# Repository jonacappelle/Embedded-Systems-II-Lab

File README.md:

# LAB: Embedded Systems II

## SOFTWARE

- [IMU](https://github.com/jonacappelle/Embedded-Systems-II-Lab/tree/master/Jona%20-%20IMU%20and%20Main%20PCB/Embedded_II_ICM_20948)
- [Game](https://github.com/jonacappelle/Embedded-Systems-II-Lab/tree/master/Niels%20-%20Code%20spel/SLSTK3400A_blink)
- [LoRa](https://github.com/jonacappelle/Embedded-Systems-II-Lab/tree/master/Pieter%20-%20Connectivity%20and%20Visualisation)

## HARDWARE

[Main board](https://github.com/jonacappelle/Embedded-Systems-II-Lab/tree/master/Jona%20-%20IMU%20and%20Main%20PCB/EFM32_ICM20948_PCB)  
[Energy harvesting](https://github.com/jonacappelle/Embedded-Systems-II-Lab/tree/master/Daan%20-%20VoedingDesign%20PCB/schema_pcb)

### MAIN BOARD: µC + Compass + LoRa

### POWER BOARD

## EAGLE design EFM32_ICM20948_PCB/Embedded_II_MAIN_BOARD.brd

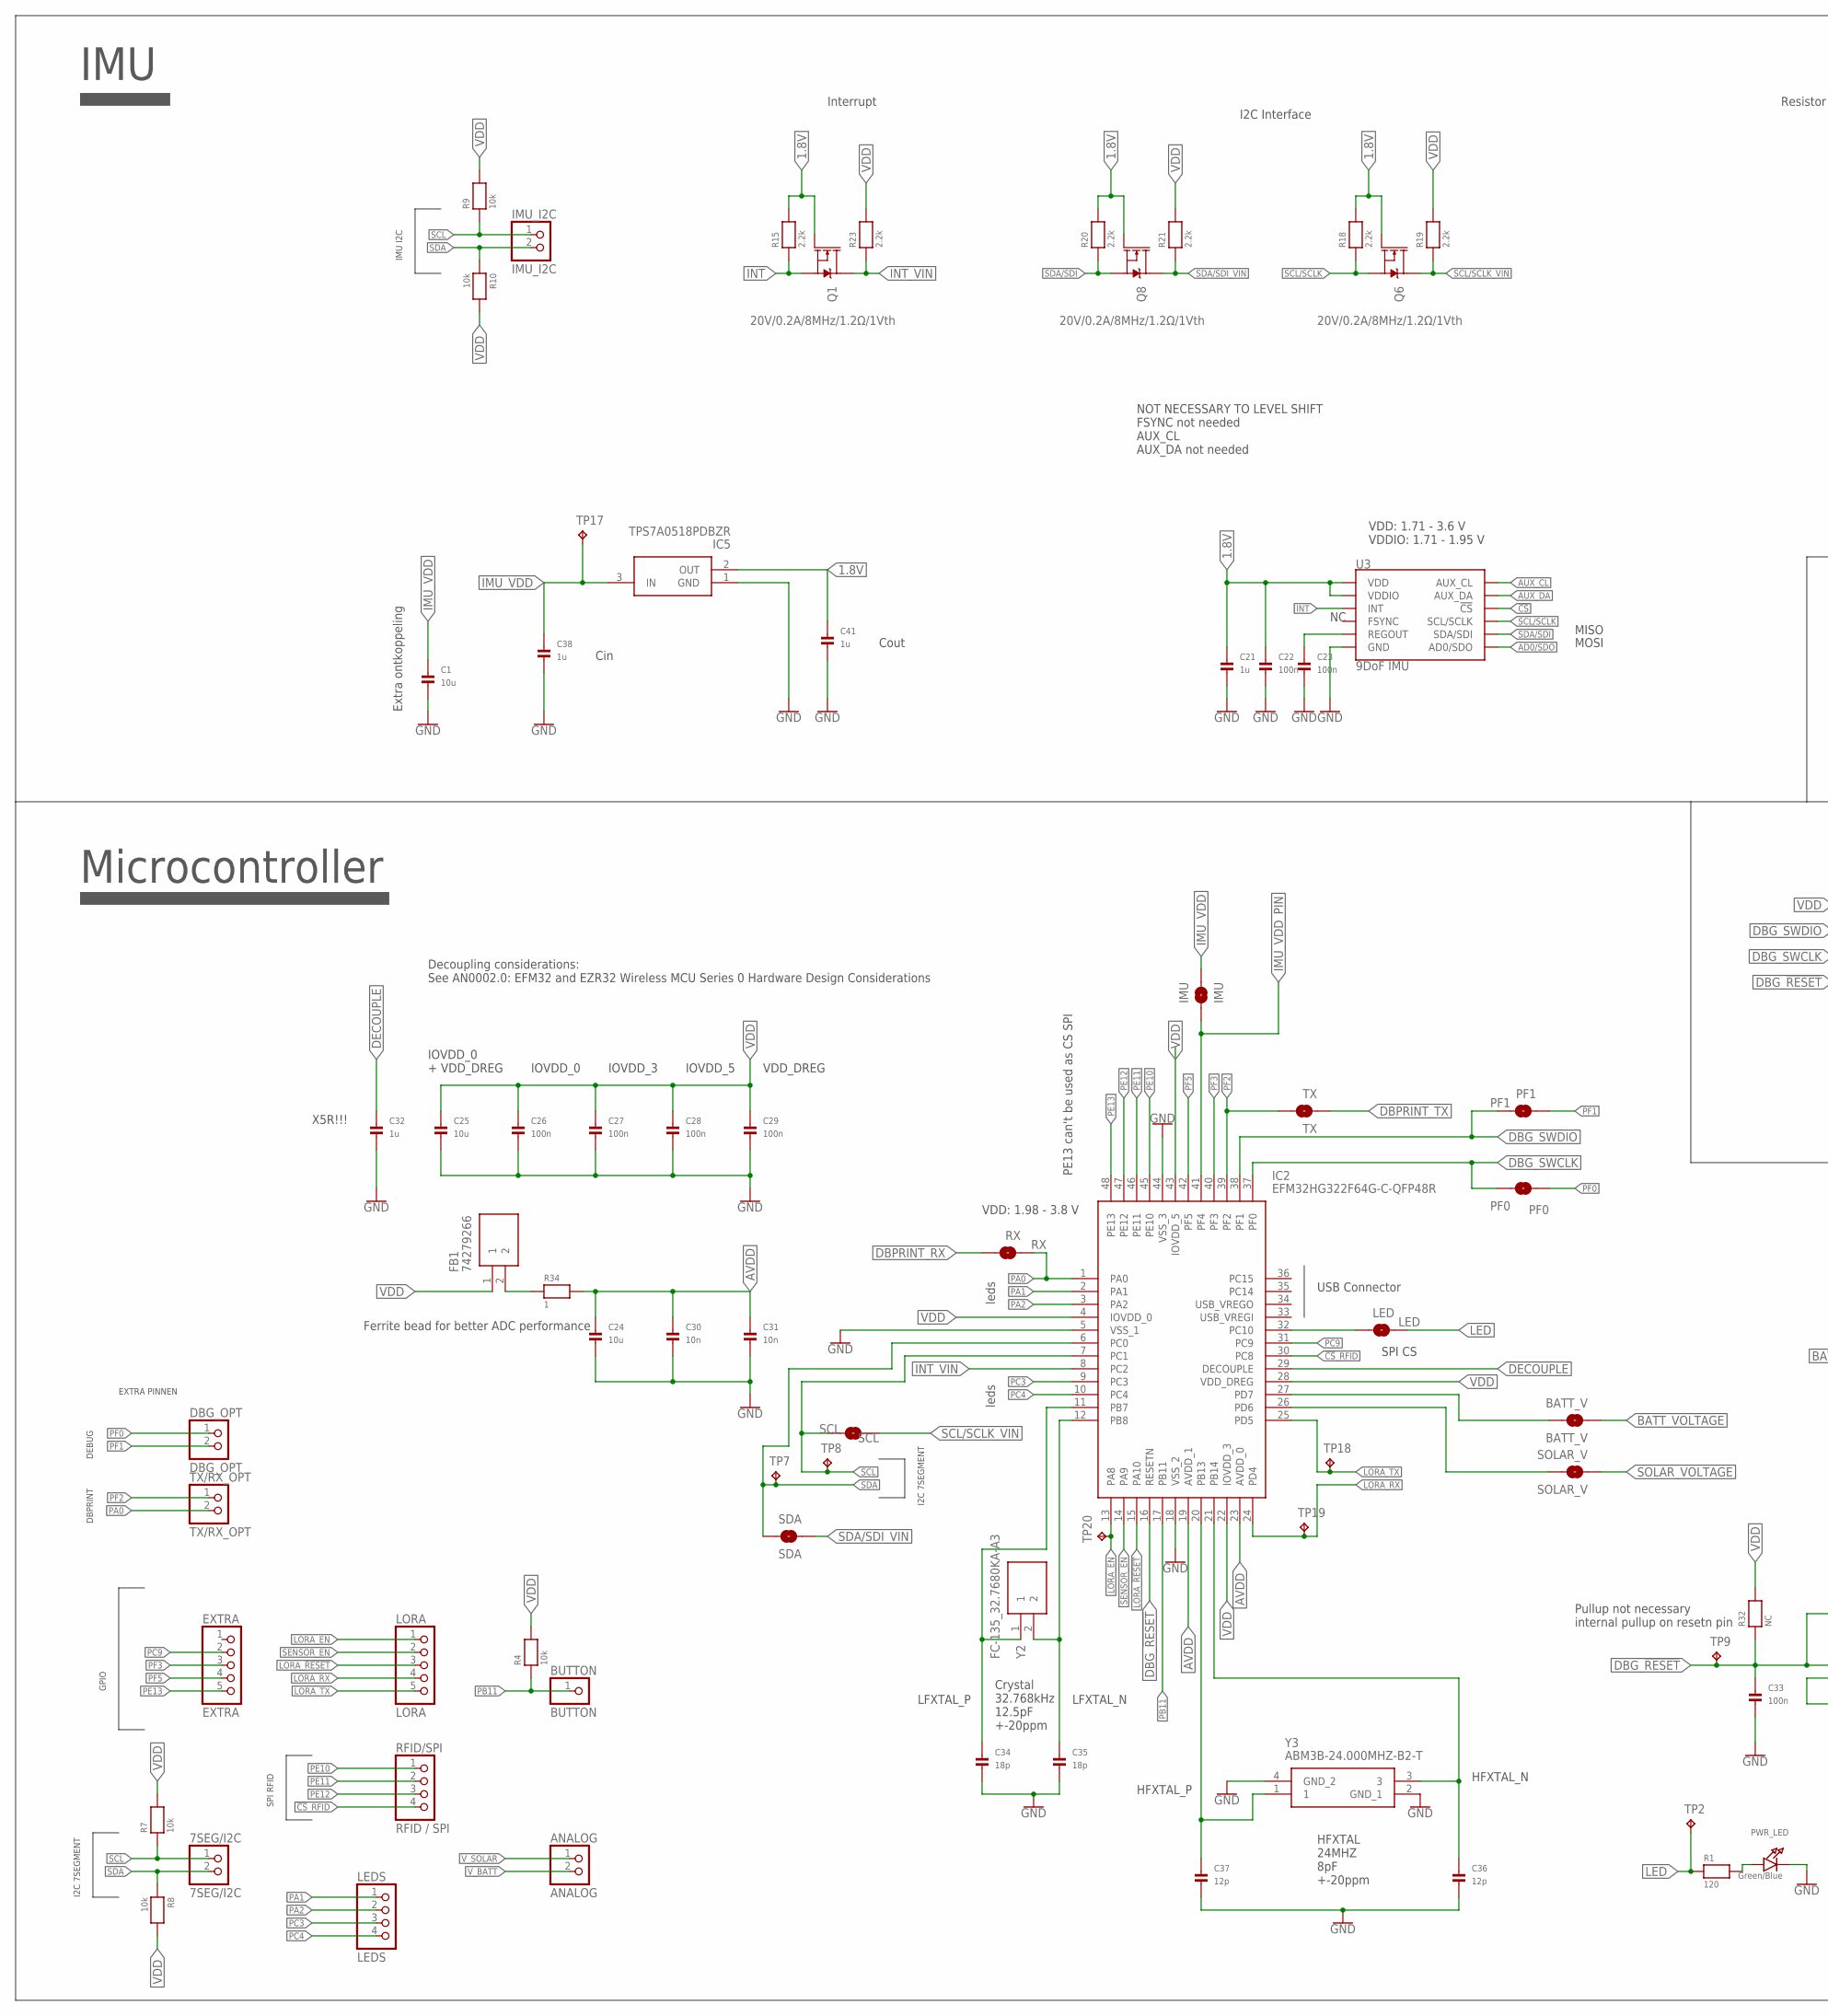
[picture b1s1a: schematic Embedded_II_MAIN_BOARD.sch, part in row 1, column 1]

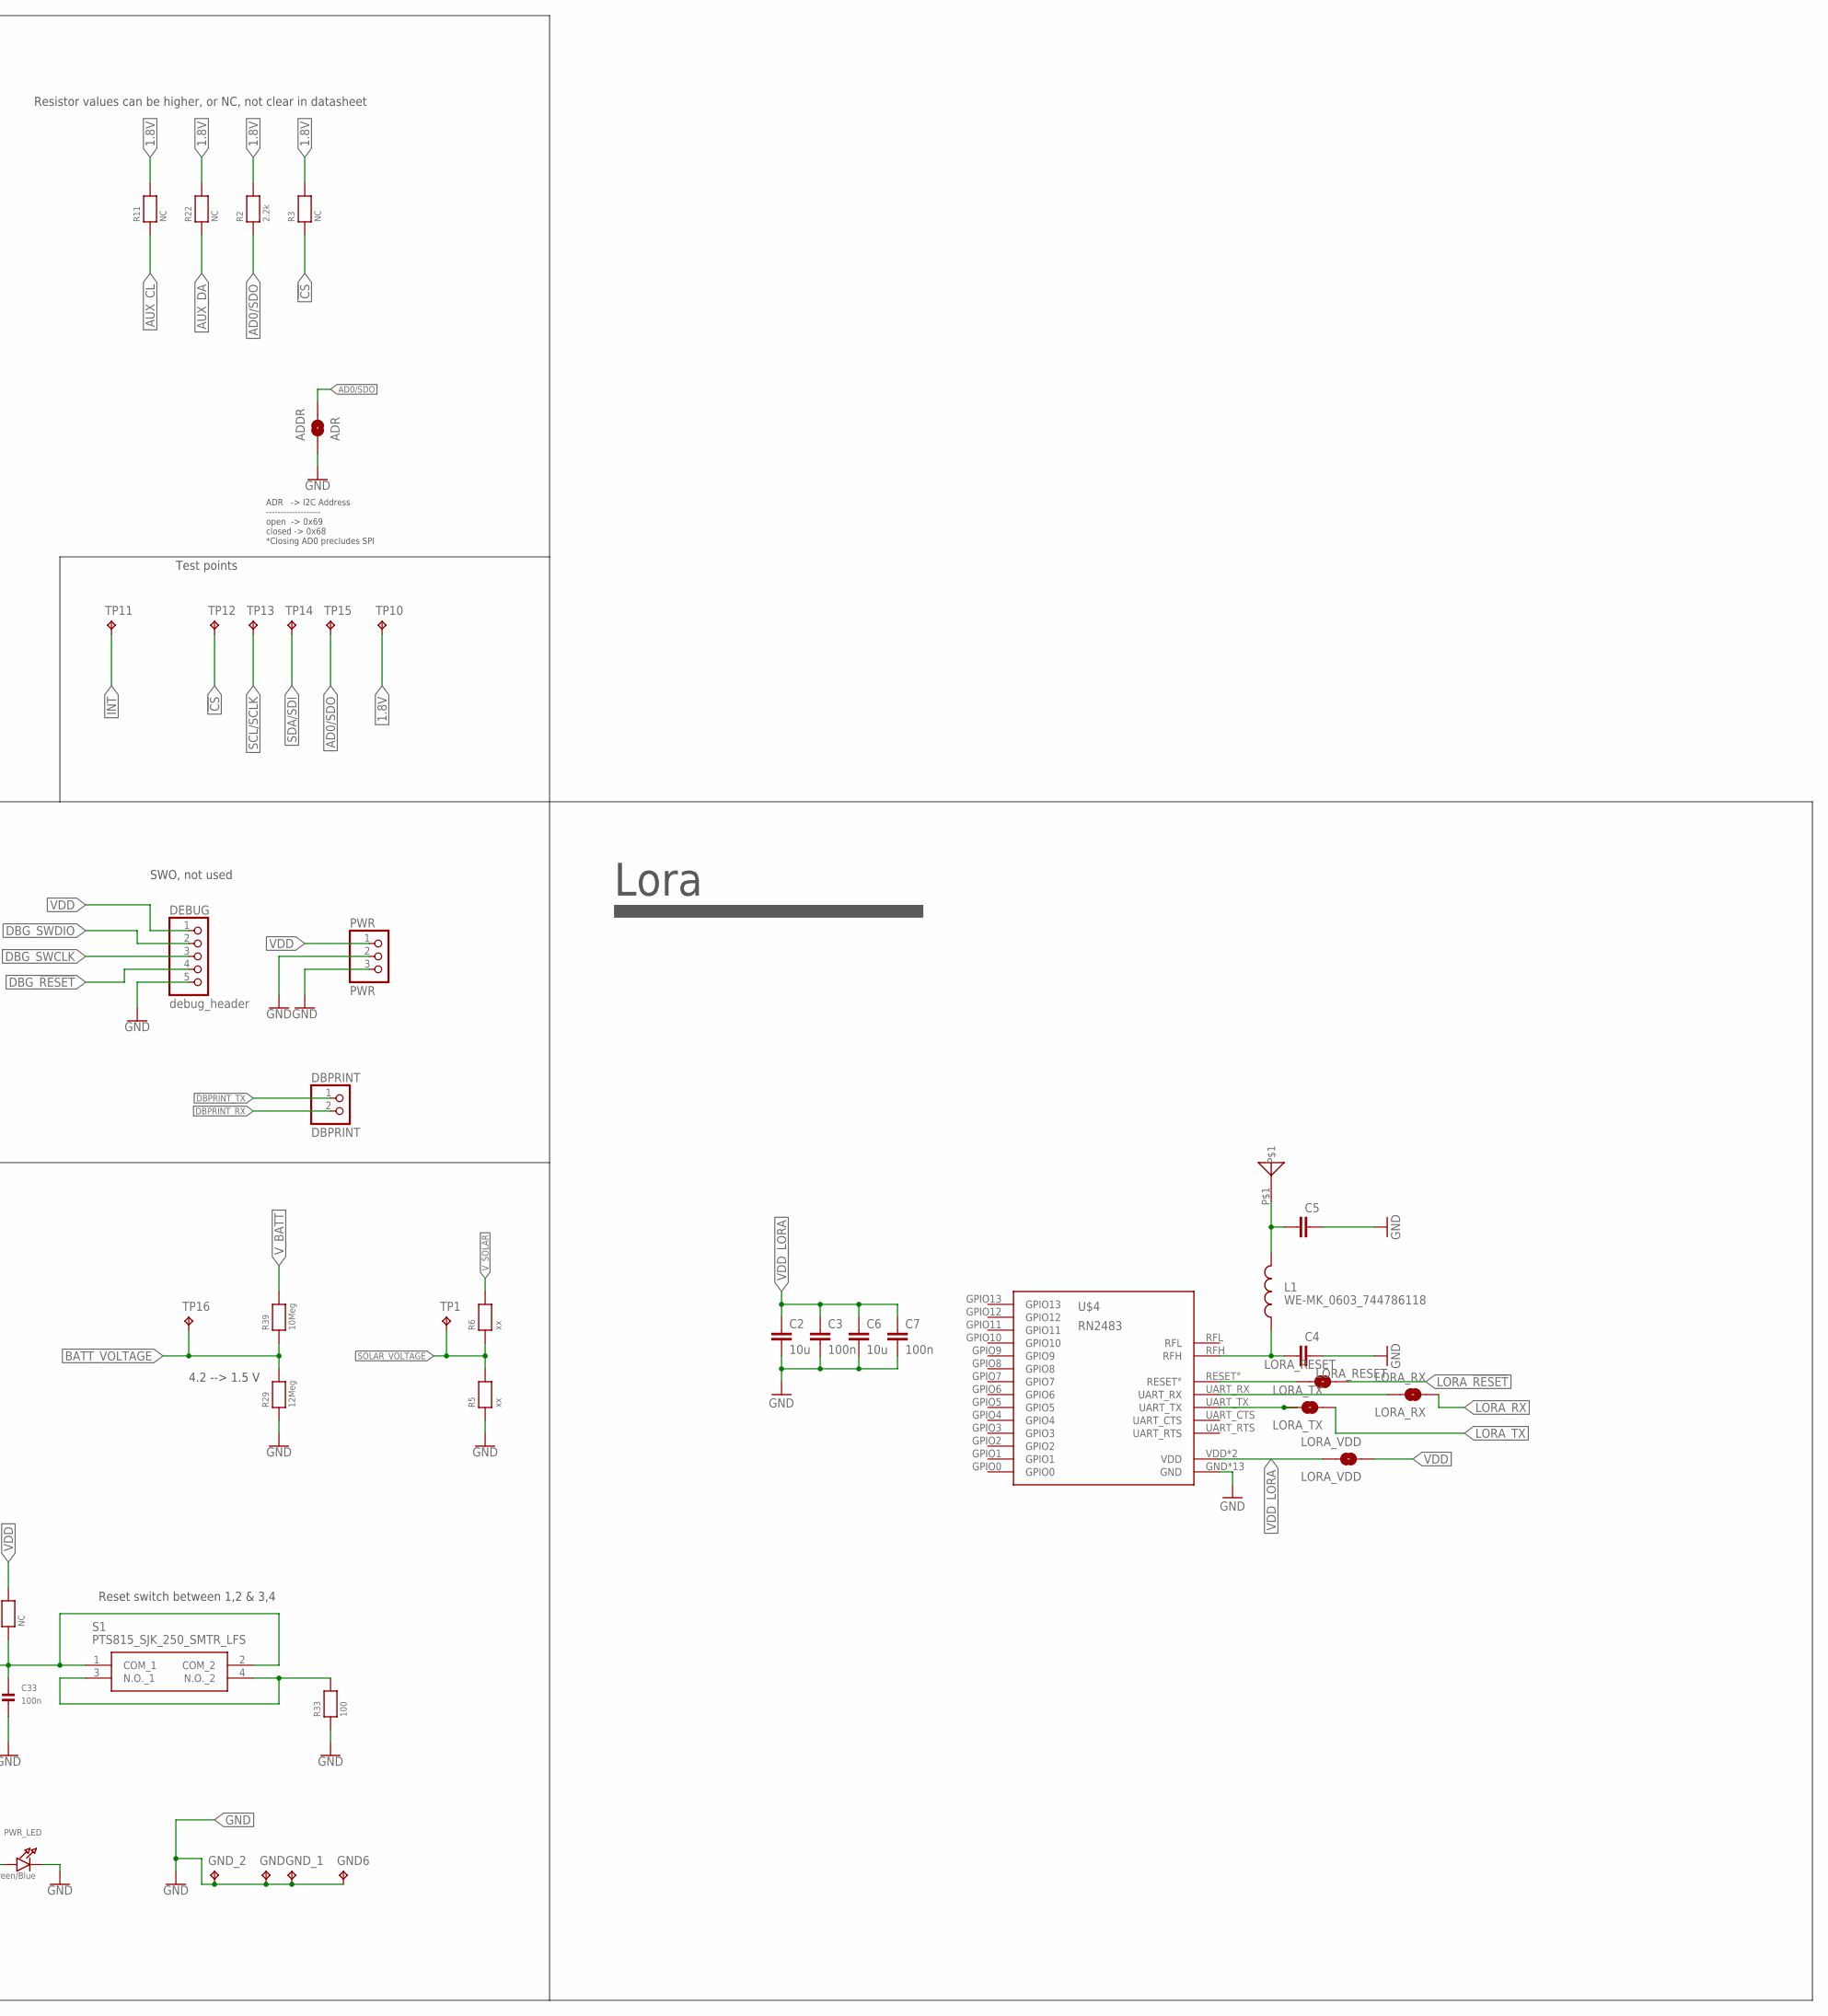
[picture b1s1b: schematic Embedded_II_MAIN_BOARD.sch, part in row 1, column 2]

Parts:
7SEG/I2C: 7SEG/I2C; 1X02
ADDR: ADR; SMT-JUMPER_2_NO_SILK
ANALOG: ANALOG; 1X02
BATT_V: BATT_V; SMT-JUMPER_2_NO_SILK
BUTTON: BUTTON; 1X01
C1, C24, C25: 10u; 0603
C2, C6: 10u; C0805K
C3, C7: 100n; C0805K
C4, C5: C-EUC0603K; C0603K
C21, C32, C38, C41: 1u; 0603
C22, C23, C26, C27, C28, C29, C33: 100n; 0603
C30, C31: 10n; 0603
C34, C35: 18p; 0603
C36, C37: 12p; 0603
DBG_OPT: DBG_OPT; 1X02
DBPRINT: DBPRINT; 1X02
DEBUG: debug_header; 1X05
EXTRA: EXTRA; 1X05
FB1: 74279266; BEADC1608X100N
GND, GND6: TPTP20SQ; TP20SQ
GND_1, GND_2: TPTP20SQ; TP20SQ
IC2: EFM32HG322F64G-C-QFP48R; QFP50P900X900X120-48N
IC5: TPS7A0518PDBZR; SOT95P237X112-3N
IMU: IMU; SMT-JUMPER_2_NO_SILK
IMU_I2C: IMU_I2C; 1X02
L1: WE-MK_0603_744786118; WE-MK_0603
LED: LED; SMT-JUMPER_2_NO_SILK
LEDS: LEDS; 1X04
LORA: LORA; 1X05
LORA_RESET: LORA_RESET; SMT-JUMPER_2_NO_SILK
LORA_RX: LORA_RX; SMT-JUMPER_2_NO_SILK
LORA_TX: LORA_TX; SMT-JUMPER_2_NO_SILK
LORA_VDD: LORA_VDD; SMT-JUMPER_2_NO_SILK
PF0: PF0; SMT-JUMPER_2_NO_SILK
PF1: PF1; SMT-JUMPER_2_NO_SILK
PWR: PWR; 1X03
PWR_LED: Green/Blue; CHIPLED_0805
Q1, Q6, Q8: 20V/0.2A/8MHz/1.2Ω/1Vth; SOT-416FL
R1: 120; 0603
R2, R15, R18, R19, R20, R21, R23: 2.2k; 0603
R3, R11, R22, R32: NC; 0603
R4, R7, R8, R9, R10: 10k; 0603
R5, R6: xx; 0603
R29: 12Meg; 0603
R33: 100; 0603
R34: 1; 0603
R39: 10Meg; 0603
RFID/SPI: RFID / SPI; 1X04
RX: RX; SMT-JUMPER_2_NO_SILK
S1: PTS815_SJK_250_SMTR_LFS; PTS815SJK250SMTRLFS
SCL: SCL; SMT-JUMPER_2_NO_SILK
SDA: SDA; SMT-JUMPER_2_NO_SILK
SOLAR_V: SOLAR_V; SMT-JUMPER_2_NO_SILK
TP1, TP2, TP7, TP8, TP9, TP10, TP11, TP12, TP13, TP14, TP15, TP16, TP17, TP18, TP19, TP20: TPTP10R; TP10R
TX: TX; SMT-JUMPER_2_NO_SILK
TX/RX_OPT: TX/RX_OPT; 1X02
U3: 9DoF IMU; SPARKFUN-SENSORS_QFN24-3X3
U$2: ANTENNA868; CERAMIC-ANTENNA
U$4: RN2483
Y2: FC-135_32.7680KA-A3; FC135327680KAAG0
Y3: ABM3B-24.000MHZ-B2-T; ABM3B8000MHZ101UT

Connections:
1.8V: C21.1, C22.1, C41.1, IC5.2 (OUT), Q1.1 (G), Q6.1 (G), Q8.1 (G), R2.2, R3.2, R11.2, R15.2, R18.2, R20.2, R22.2, TP10.TP, U3.8 (VDDIO), U3.13 (VDD)
!CS: R3.1, TP12.TP, U3.22 (!CS)
!CS!_RFID: IC2.30 (PC8), RFID/SPI.4
AD0/SDO: ADDR.2, R2.1, TP15.TP, U3.9 (AD0/SDO)
AUX_CL: R11.1, U3.7 (AUX_CL)
AUX_DA: R22.1, U3.21 (AUX_DA)
AVDD: C24.1, C30.1, C31.1, IC2.19 (AVDD_1), IC2.23 (AVDD_0), R34.2
BATT_VOLTAGE: BATT_V.1, R29.2, R39.1, TP16.TP
DBG_!RESET: C33.1, DEBUG.4, IC2.16 (RESETN), R32.1, S1.1 (COM_1), S1.2 (COM_2), TP9.TP
DBG_SWCLK: DEBUG.3, IC2.37 (PF0), PF0.2
DBG_SWDIO: DEBUG.2, IC2.38 (PF1), PF1.2
DBPRINT_RX: DBPRINT.2, RX.2
DBPRINT_TX: DBPRINT.1, TX.1
DECOUPLE: C32.1, IC2.29 (DECOUPLE)
GND: ADDR.1, C1.2, C2.2, C3.2, C4.1, C5.1, C6.2, C7.2, C21.2, C22.2, C23.2, C24.2, C25.2, C26.2, C27.2, C28.2, C29.2, C30.2, C31.2, C32.2, C33.2, C34.2, C35.2, C36.2, C37.2, C38.2, C41.2, DEBUG.5, GND.TP, GND6.TP, GND_1.TP, GND_2.TP, IC2.5 (VSS_1), IC2.18 (VSS_2), IC2.44 (VSS_3), IC5.1 (GND), PWR.2, PWR.3, PWR_LED.C, R5.1, R29.1, R33.1, U3.18 (GND), U3.20 (GND), U$4.GND, Y3.2 (GND_1), Y3.4 (GND_2); also elsewhere on the board
IMU_VDD: C1.1, C38.1, IC5.3 (IN), IMU.1, TP17.TP
IMU_VDD_PIN: IC2.41 (PF4), IMU.2
INT: Q1.2 (S), R15.1, TP11.TP, U3.12 (INT)
INT_VIN: IC2.8 (PC2), Q1.3 (D), R23.1
LED: LED.1, R1.1, TP2.TP
LORA_!RESET!: IC2.15 (PA10), LORA.3, LORA_RESET.1
LORA_RX: IC2.24 (PD4), LORA.4, LORA_RX.1, TP19.TP
LORA_TX: IC2.25 (PD5), LORA.5, LORA_TX.1, TP18.TP
unnamed: C5.2, L1.2, U$2.P$1
unnamed 24: C4.2, L1.1, U$4.RFH; also elsewhere on the board
unnamed: PWR_LED.A, R1.2
unnamed: IC2.32 (PC10), LED.2
unnamed 27: LORA_RX.2, U$4.UART_RX; also elsewhere on the board
unnamed 28: LORA_TX.2, U$4.UART_TX; also elsewhere on the board
unnamed 29: LORA_RESET.2, U$4.RESET°; also elsewhere on the board
unnamed: C35.1, IC2.12 (PB8), Y2.2
unnamed: C23.1, U3.10 (REGOUT)
unnamed: C34.1, IC2.11 (PB7), Y2.1
unnamed: C37.1, IC2.20 (PB13), Y3.1
unnamed: C36.1, IC2.21 (PB14), Y3.3
unnamed: R33.2, S1.3 (N.O._1), S1.4 (N.O._2)
unnamed: FB1.2, R34.1
PA0: IC2.1 (PA0), RX.1, TX/RX_OPT.2
PA1: IC2.2 (PA1), LEDS.1
PA2: IC2.3 (PA2), LEDS.2
PA8: IC2.13 (PA8), LORA.1, TP20.TP; also elsewhere on the board
PA9: IC2.14 (PA9), LORA.2; also elsewhere on the board
PB11: BUTTON.1, IC2.17 (PB11), R4.1
PC3: IC2.9 (PC3), LEDS.3
PC4: IC2.10 (PC4), LEDS.4
PC9: EXTRA.2, IC2.31 (PC9)
PD6: IC2.26 (PD6), SOLAR_V.2
PD7: BATT_V.2, IC2.27 (PD7)
PE10: IC2.45 (PE10), RFID/SPI.1
PE11: IC2.46 (PE11), RFID/SPI.2
PE12: IC2.47 (PE12), RFID/SPI.3
PE13: EXTRA.5, IC2.48 (PE13)
PF0: DBG_OPT.1, PF0.1
PF1: DBG_OPT.2, PF1.1
PF2: IC2.39 (PF2), TX.2, TX/RX_OPT.1
PF3: EXTRA.3, IC2.40 (PF3)
PF5: EXTRA.4, IC2.42 (PF5)
SCL: 7SEG/I2C.1, IC2.7 (PC1), IMU_I2C.1, R7.1, R9.1, SCL.2, TP8.TP
SCL/SCLK: Q6.2 (S), R18.1, TP13.TP, U3.23 (SCL/SCLK)
SCL/SCLK_VIN: Q6.3 (D), R19.1, SCL.1
SDA: 7SEG/I2C.2, IC2.6 (PC0), IMU_I2C.2, R8.1, R10.1, SDA.2, TP7.TP
SDA/SDI: Q8.2 (S), R20.1, TP14.TP, U3.24 (SDA/SDI)
SDA/SDI_VIN: Q8.3 (D), R21.1, SDA.1
SOLAR_VOLTAGE: R5.2, R6.1, SOLAR_V.1, TP1.TP
VDD: C25.1, C26.1, C27.1, C28.1, C29.1, DEBUG.1, FB1.1, IC2.4 (IOVDD_0), IC2.22 (IOVDD_3), IC2.28 (VDD_DREG), IC2.43 (IOVDD_5), LORA_VDD.1, PWR.1, R4.2, R7.2, R8.2, R9.2, R10.2, R19.2, R21.2, R23.2, R32.2
VDD_LORA: C2.1, C3.1, C6.1, C7.1, LORA_VDD.2, U$4.VDD; also elsewhere on the board
V_BATT: ANALOG.2, R39.2
V_SOLAR: ANALOG.1, R6.2

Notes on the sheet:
IMU
Microcontroller
ADR -> I2C Address ------------------- open -> 0x69 closed -> 0x68 *Closing AD0 precludes SPI
VDD: 1.71 - 3.6 V VDDIO: 1.71 - 1.95 V
USB Connector
X5R!!!
Crystal 32.768kHz 12.5pF +-20ppm
HFXTAL 24MHZ 8pF +-20ppm
HFXTAL_P
HFXTAL_N
LFXTAL_P
LFXTAL_N
Reset switch between 1,2 & 3,4
Ferrite bead for better ADC performance
IOVDD_0 + VDD_DREG
IOVDD_0
IOVDD_3
IOVDD_5
Decoupling considerations: See AN0002.0: EFM32 and EZR32 Wireless MCU Series 0 Hardware Design Considerations
Pullup not necessary internal pullup on resetn pin
VDD: 1.98 - 3.8 V
Cin
Cout
PE13 can't be used as CS SPI
NOT NECESSARY TO LEVEL SHIFT FSYNC not needed AUX_CL AUX_DA not needed
MISO
MOSI
VDD_DREG
SWO, not used
Resistor values can be higher, or NC, not clear in datasheet
I2C Interface
Interrupt
Test points
Extra ontkoppeling
SPI RFID
GPIO
I2C 7SEGMENT
DBPRINT
DEBUG
4.2 --> 1.5 V

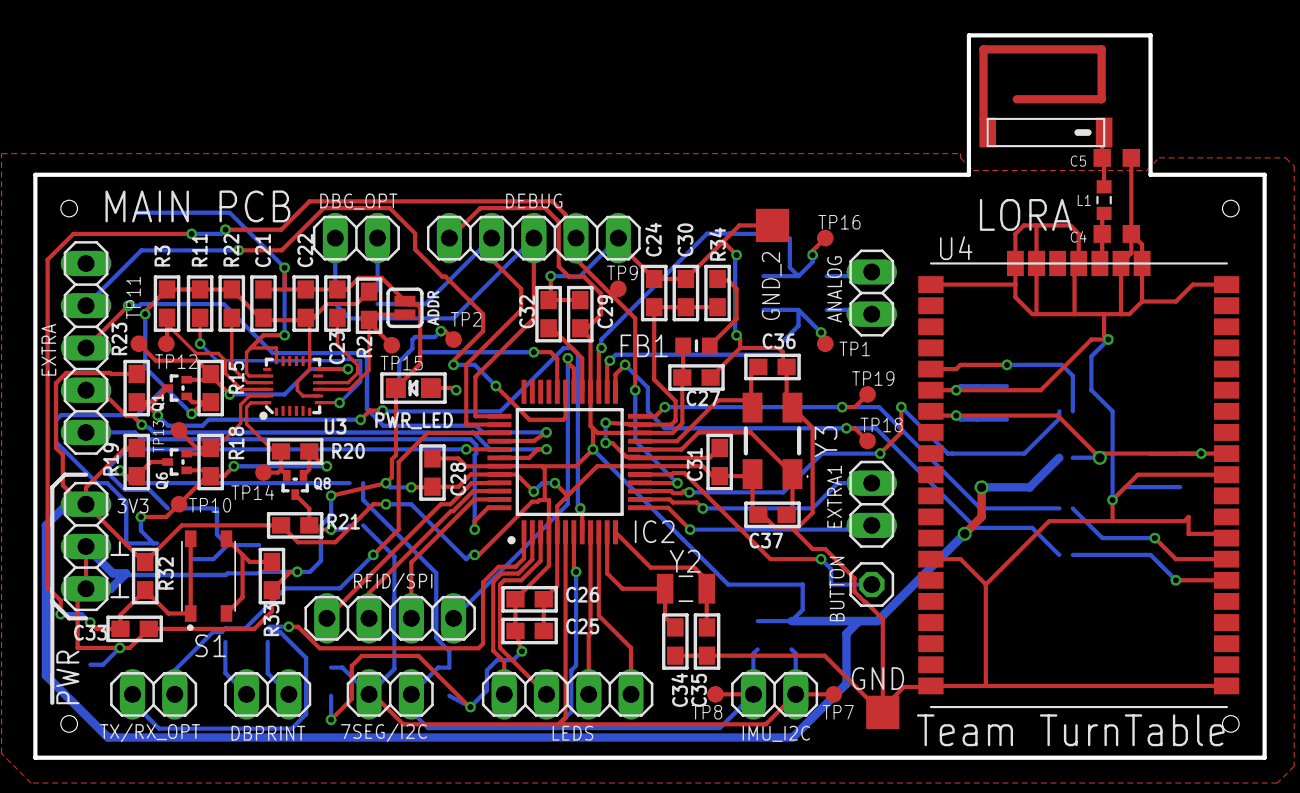
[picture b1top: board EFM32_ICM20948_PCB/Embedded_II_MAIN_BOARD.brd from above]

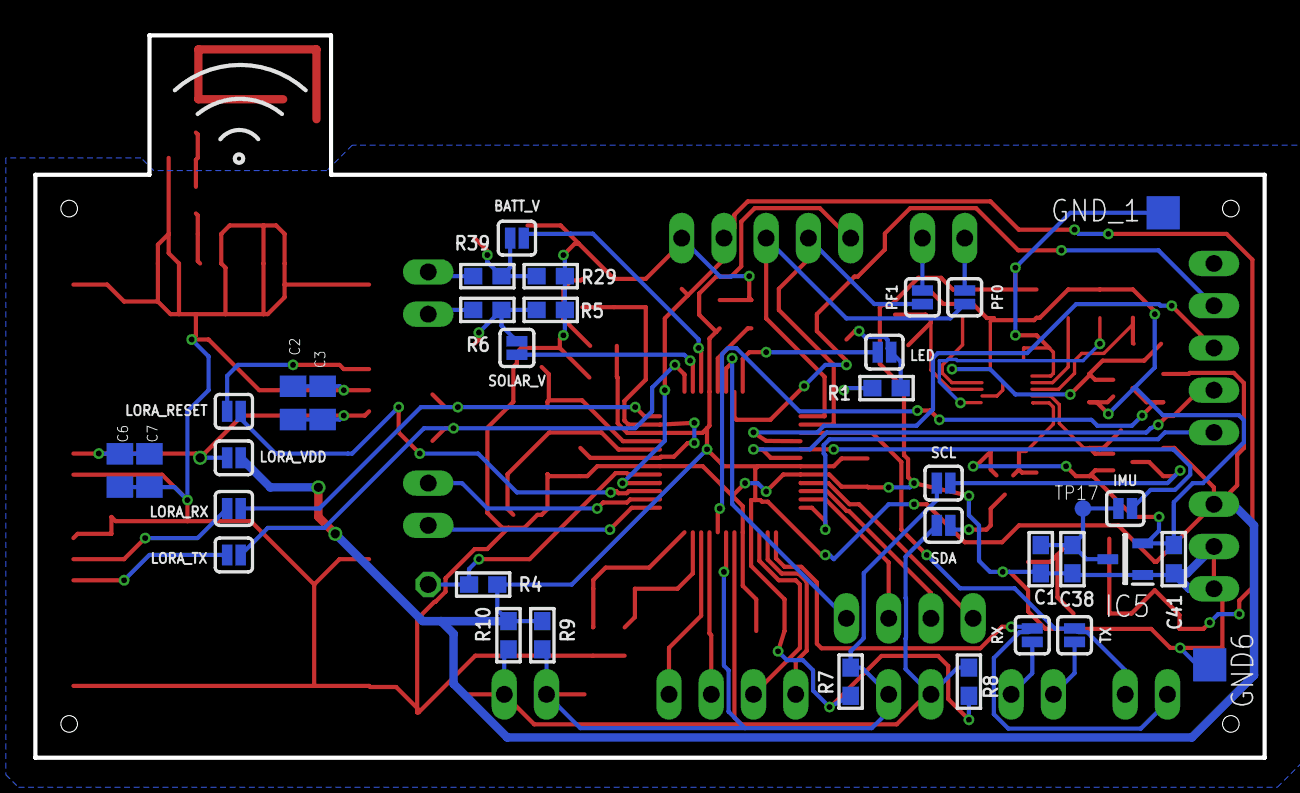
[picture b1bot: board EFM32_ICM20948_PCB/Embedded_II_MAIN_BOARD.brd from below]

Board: 2 copper layers, 73.9 x 43.4 mm, 110 parts (35 on the bottom side), 68 nets.

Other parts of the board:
EXTRA1: EXTRA; 1X02
U4: RN2483

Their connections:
GND: U4.GND, U4.GND1, U4.GND2, U4.GND3, U4.GND4, U4.GND5, U4.GND6, U4.GND7, U4.GND8, U4.GND9, U4.GND10, U4.GND11, U4.GND12; also elsewhere on the board
unnamed 24: U4.RFH; also elsewhere on the board
unnamed 27: U4.UART_RX; also elsewhere on the board
unnamed 28: U4.UART_TX; also elsewhere on the board
unnamed 29: U4.RESET°; also elsewhere on the board
PA8: EXTRA1.1; also elsewhere on the board
PA9: EXTRA1.2; also elsewhere on the board
VDD_LORA: U4.VDD, U4.VDD2; also elsewhere on the board

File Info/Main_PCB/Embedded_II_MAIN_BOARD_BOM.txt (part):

------------------------------------------------
Team Turn Table BOM Main PCB: Kompas + uC + LoRa
------------------------------------------------
Dit is het minimaal aantal nodige componenten.
Best enkele extras voorzien a.u.b.
------------------------------------------------

Qty Value                   Device                     Package                    Parts                                                                               Description                                                                                                                     DESCRIPTION                                                                                                                     HEIGHT MANUFACTURER_NAME MANUFACTURER_PART_NUMBER MOUSER_PART_NUMBER   MOUSER_PRICE-STOCK                                                     PROD_ID     SPICEPREFIX TP_SIGNAL_NAME VALUE                  

-------------
 Capacitors
-------------
Op de campus:
9   100n                    CAP_CERAMIC0603            0603                       C22, C23, C26, C27, C28, C29, C33, C3, C7                                           Ceramic Capacitors                                                                                                                                                                                                                                                                                                                                                                                                                                                          
2   10n                     CAP_CERAMIC0603            0603                       C30, C31                                                                            Ceramic Capacitors                                                                                                                                                                                                                                                                                                                                                                                                                                                          
2   10u                     C-EUC0805K                 C0805K                     C2, C6                                                                              CAPACITOR, European symbol                                                                                                                                                                                                                                                                                                                                                                                                C                                                 
3   10u                     CAP_CERAMIC0603            0603                       C1, C24, C25                                                                        Ceramic Capacitors                                                                                                                                                                                                                                                                                                                                                                                                                                                          
2   12p                     CAP_CERAMIC0603            0603                       C36, C37                                                                            Ceramic Capacitors                                                                                                                                                                                                                                                                                                                                                                                                                                                          
4   1u                      CAP_CERAMIC0603            0603                       C21, C32, C38, C41                                                                  Ceramic Capacitors                                                                                                                                                                                                                                                                                                                                                                                                                                                          

Bestellen:
2   18p                     CAP_CERAMIC0603            0603                       C34, C35                                                                            Ceramic Capacitors                                                                                                                                                                                                                                                                                                                                                                                                                                                          
https://www.mouser.be/ProductDetail/KEMET/C0603C180K5RACTU?q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

------------
 Weerstanden
------------
Op de campus:
1   220K                    RESISTOR0603               0603                       R5                                                                                  Resistors       
7   2.2k/2k ook goed        RESISTOR0603               0603                       R2, R15, R18, R19, R20, R21, R23                                                    Resistors                                                                                                                                                                                                                                                                                                                                                                                                                                                                   
1   10Meg                   RESISTOR0603               0603                       R39                                                                                 Resistors                                                                                                                                                                                                                                                                                                                                                                                                                                                                   
5   10k                     RESISTOR0603               0603                       R4, R7, R8, R9, R10                                                                 Resistors                                                                                                                                                                                                                                                                                                                                                                                                                                                                   
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

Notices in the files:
parts and their libraries:
microbuilder: This work is placed in the public domain, and may be freely used for commercial and non-commercial work with the following conditions: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
SparkFun-Jumpers: Licensing: Creative Commons ShareAlike 4.0 International - https://creativecommons.org/licenses/by-sa/4.0
